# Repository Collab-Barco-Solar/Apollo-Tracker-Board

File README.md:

# Apollo-Tracker-Board
 
Projetos das PCB de transmissores e receptores, criadas no software KICAD 5.1.6.

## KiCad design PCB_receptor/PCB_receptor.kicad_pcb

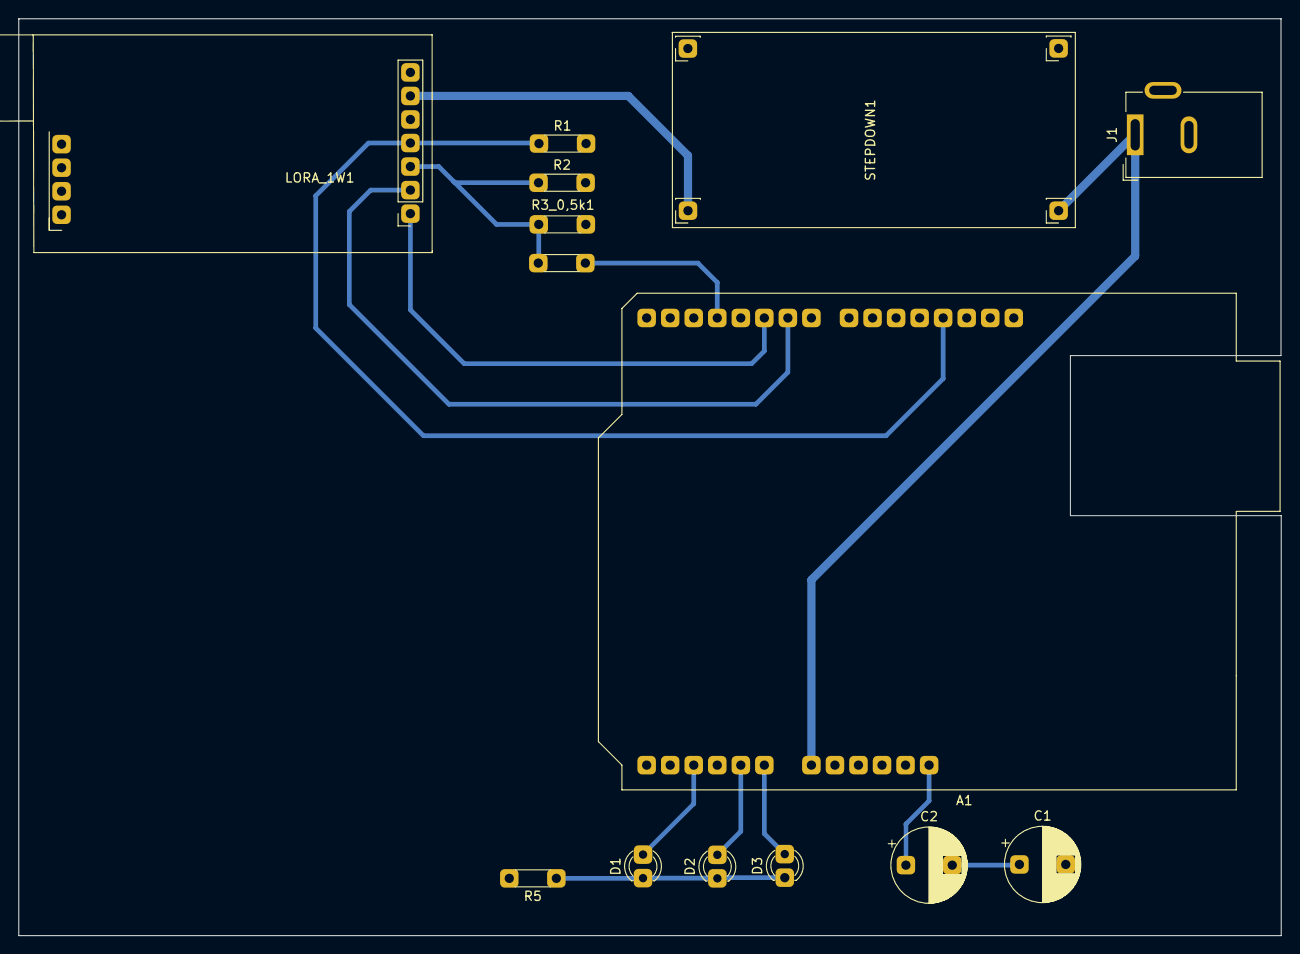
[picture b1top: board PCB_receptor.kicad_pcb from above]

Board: 2 copper layers, 136.2 x 98.9 mm, 14 parts (0 on the bottom side), 14 nets.

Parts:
1k1: R4_1k; R_Axial_DIN0204_L3.6mm_D1.6mm_P5.08mm_Horizontal
A1: Board_Ethernet_Shield_W5100-Arduino_Mega; Ethernet_Shield_W5100
C1, C2: 0,1uF; CP_Radial_D8.0mm_P5.00mm
D1, D2, D3: LED; LED_D3.0mm
J1: Barrel_Jack_MountingPin; BarrelJack_Wuerth_6941xx301002
LORA_1W1: LORA_433T30D; LORA_E32_433T30D
R1, R2: 4K7; R_Axial_DIN0204_L3.6mm_D1.6mm_P5.08mm_Horizontal
R3_0,5k1: R; R_Axial_DIN0204_L3.6mm_D1.6mm_P5.08mm_Horizontal
R5: 100; R_Axial_DIN0204_L3.6mm_D1.6mm_P5.08mm_Horizontal
STEPDOWN1: Converter_DCDC_STEPDOWN; STEPDOWN_XL4005

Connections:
3.3V_DCDC: LORA_1W1.6, STEPDOWN1.4
A0: A1.23, D3.2
A1: A1.24, D2.2
A3: A1.26, D1.2
GND: A1.2, A1.20, A1.21, C1.2, J1.2, LORA_1W1.7, R1.2, R2.2, R3_0,5k1.1, R5.2, STEPDOWN1.1, STEPDOWN1.3
GND_LED: D1.1, D2.1, D3.1, R5.1
M0: A1.11, LORA_1W1.1
M1: A1.10, LORA_1W1.2
unnamed: 1k1.2, A1.13
unnamed: C1.1, C2.2
RST: A1.17, C2.1
RX_LORA: 1k1.1, LORA_1W1.3, R2.1, R3_0,5k1.2
TX_LORA: A1.4, LORA_1W1.4, R1.1
VIN: A1.22, J1.1, STEPDOWN1.2

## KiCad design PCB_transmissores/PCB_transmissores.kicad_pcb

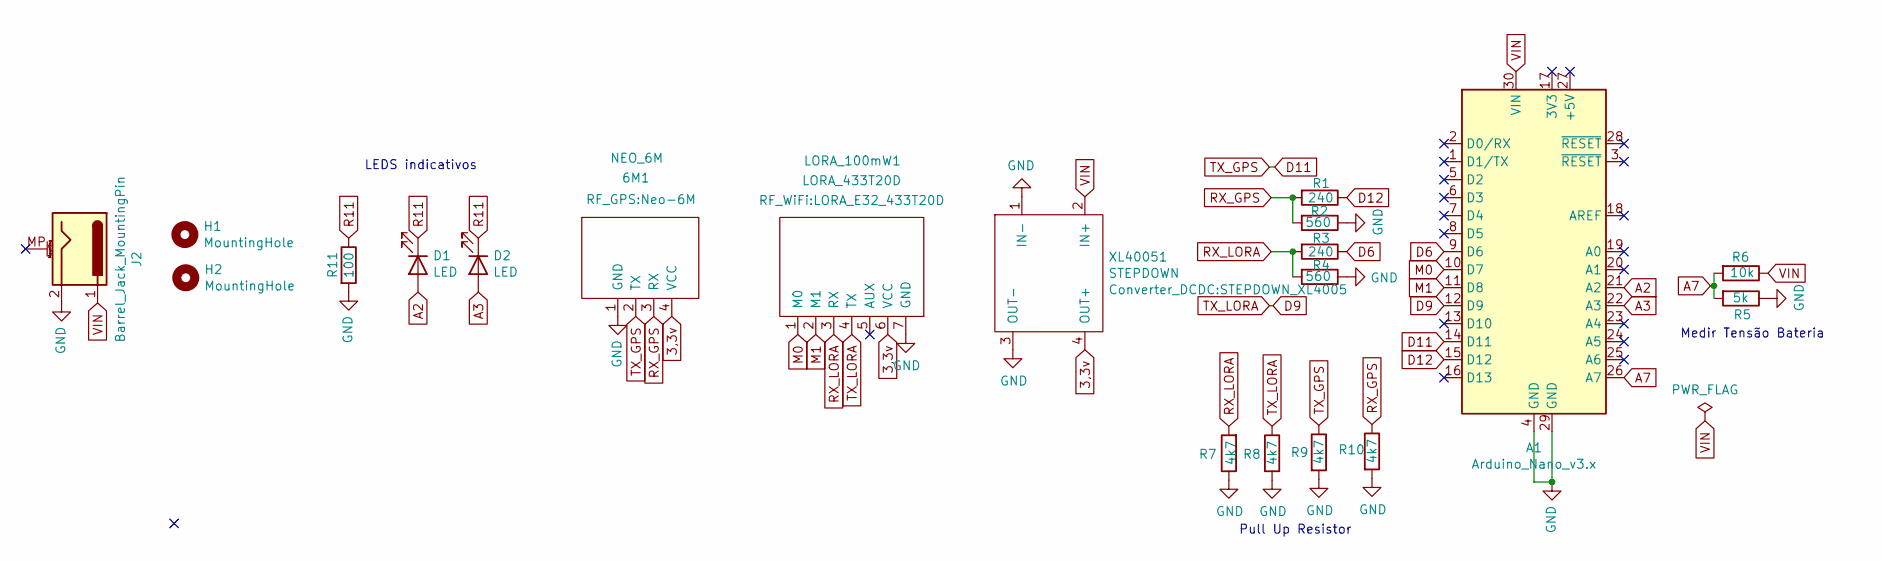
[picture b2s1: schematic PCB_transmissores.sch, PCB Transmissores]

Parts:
6M1: NEO_6M; Neo-6M
A1: Arduino_Nano_v3.x; Arduino_Nano
D1, D2: LED; LED_D5.0mm
H1, H2: MountingHole; MountingHole_5.5mm
J2: Barrel_Jack_MountingPin; BarrelJack_Wuerth_6941xx301002
LORA_100mW1: LORA_433T20D; LORA_E32_433T20D
R1, R3: 240; R_Axial_DIN0207_L6.3mm_D2.5mm_P7.62mm_Horizontal
R2, R4: 560; R_Axial_DIN0207_L6.3mm_D2.5mm_P7.62mm_Horizontal
R5: 5k; R_Axial_DIN0207_L6.3mm_D2.5mm_P7.62mm_Horizontal
R6: 10k; R_Axial_DIN0207_L6.3mm_D2.5mm_P7.62mm_Horizontal
R7, R8, R9, R10: 4k7; R_Axial_DIN0207_L6.3mm_D2.5mm_P7.62mm_Horizontal
R11: 100; R_Axial_DIN0207_L6.3mm_D2.5mm_P7.62mm_Horizontal
XL40051: STEPDOWN; STEPDOWN_XL4005

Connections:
3,3v: 6M1.4 (VCC), LORA_100mW1.6 (VCC), XL40051.4 (OUT+)
A2: A1.21 (A2), D1.2 (A)
A3: A1.22 (A3), D2.2 (A)
A7: A1.26 (A7), R5.2, R6.2
D6: A1.9 (D6), R3.1
D9: A1.12 (D9), LORA_100mW1.4 (TX), R8.1
D11: 6M1.2 (TX), A1.14 (D11), R9.1
D12: A1.15 (D12), R1.1
GND: 6M1.1 (GND), A1.4 (GND), A1.29 (GND), J2.2, LORA_100mW1.7 (GND), R2.1, R4.1, R5.1, R7.1, R8.2, R9.2, R10.2, R11.2, XL40051.1 (IN-), XL40051.3 (OUT-)
M0: A1.10 (D7), LORA_100mW1.1 (M0)
M1: A1.11 (D8), LORA_100mW1.2 (M1)
R11: D1.1 (K), D2.1 (K), R11.1
RX_GPS: 6M1.3 (RX), R1.2, R2.2, R10.1
RX_LORA: LORA_100mW1.3 (RX), R3.2, R4.2, R7.2
VIN: A1.30 (VIN), J2.1, R6.1, XL40051.2 (IN+)

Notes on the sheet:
Pull Up Resistor
Medir Tensão Bateria
LEDS indicativos

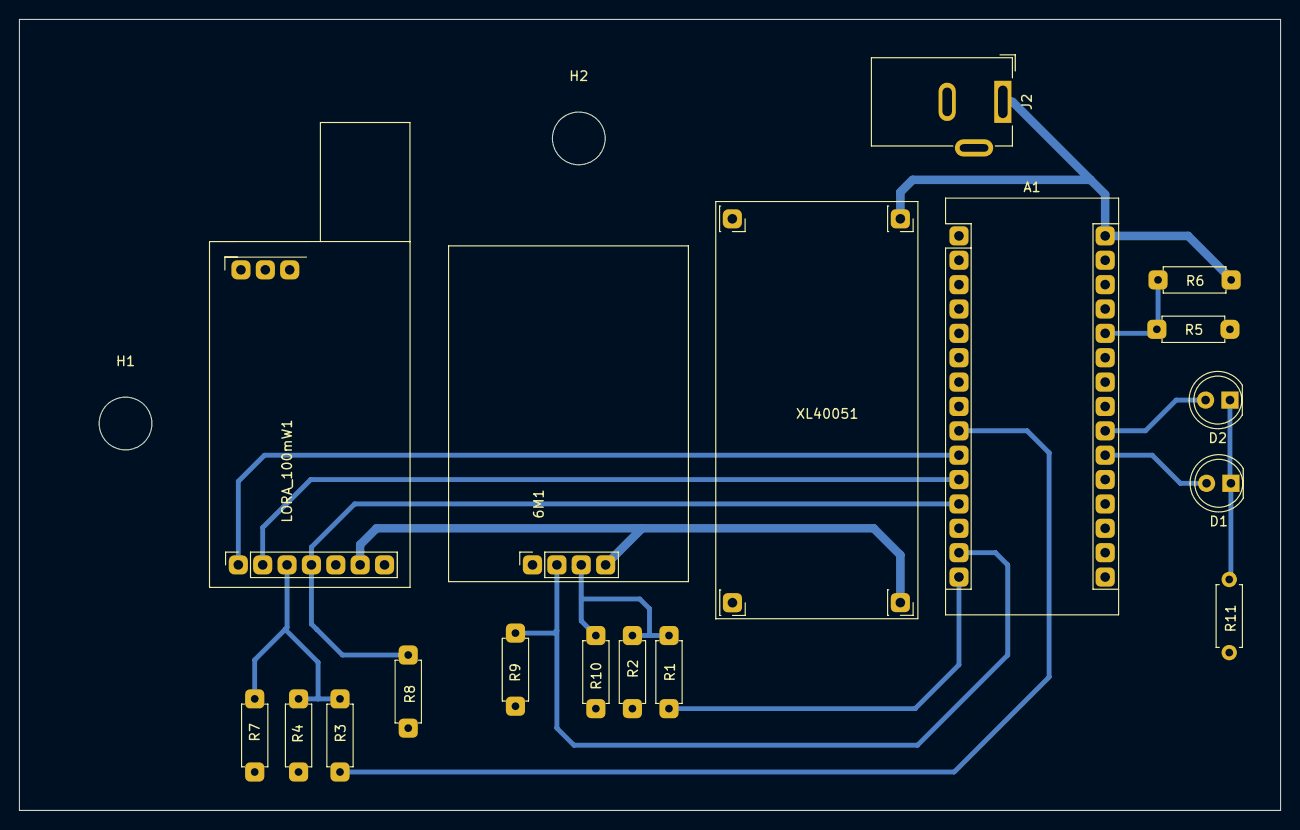
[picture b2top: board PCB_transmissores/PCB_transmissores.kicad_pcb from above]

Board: 2 copper layers, 131.4 x 82.4 mm, 20 parts (0 on the bottom side), 15 nets.

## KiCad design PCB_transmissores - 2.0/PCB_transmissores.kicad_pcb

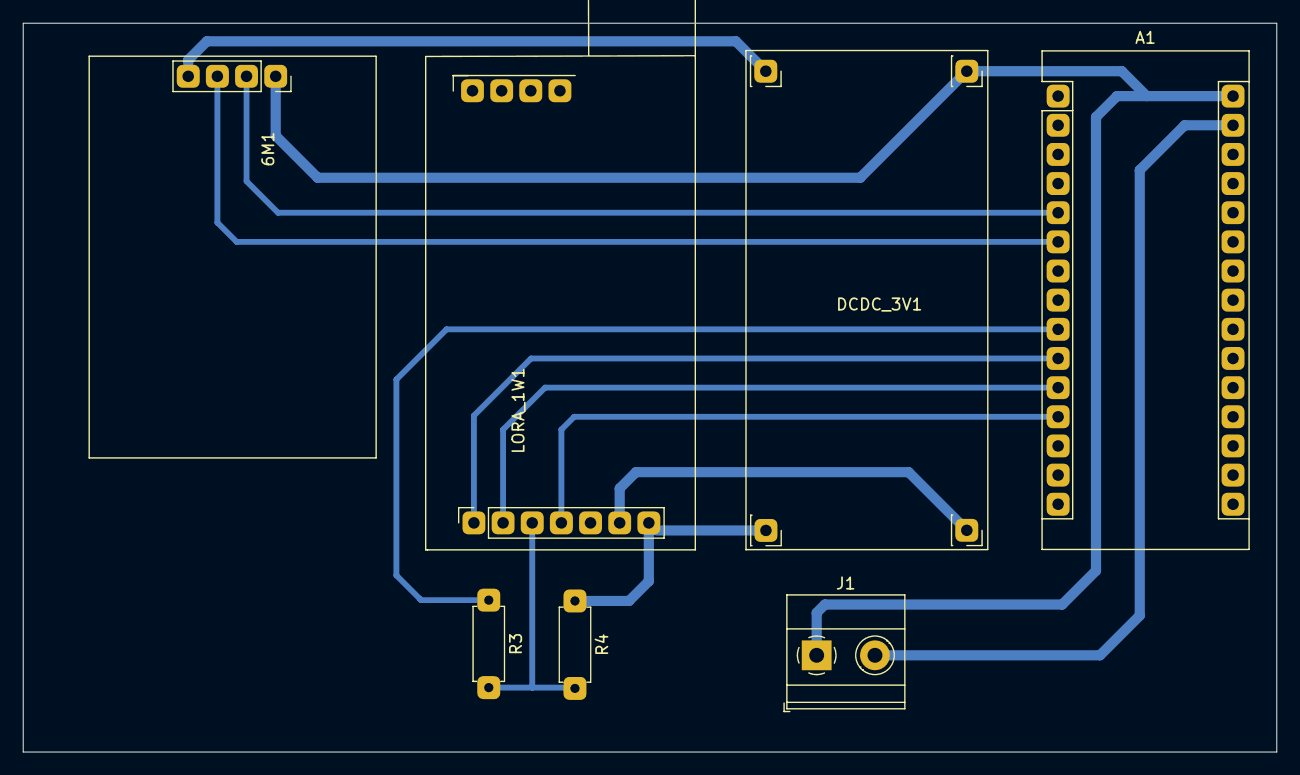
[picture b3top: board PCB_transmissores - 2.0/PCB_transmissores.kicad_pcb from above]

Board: 2 copper layers, 109.2 x 63.5 mm, 7 parts (0 on the bottom side), 10 nets.

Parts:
6M1: NEO_6M; Neo-6M
A1: Arduino_Nano_v3.x; Arduino_Nano
DCDC_3V1: DCDC_CHINA; STEPDOWN_CHINA
J1: Screw_Terminal_01x02; TerminalBlock_Phoenix_MKDS-1,5-2-5.08_1x02_P5.08mm_Horizont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
LORA_1W1: LORA_433T30D; LORA_E32_433T30D
R3: 1k; R_Axial_DIN0207_L6.3mm_D2.5mm_P7.62mm_Horizontal
R4: 0,5k; R_Axial_DIN0207_L6.3mm_D2.5mm_P7.62mm_Horizontal

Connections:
3.3V_DCDC: DCDC_3V1.4, LORA_1W1.6
GND: 6M1.1, A1.4, A1.29, DCDC_3V1.1, DCDC_3V1.3, J1.2, LORA_1W1.7, R4.1
M0: A1.10, LORA_1W1.1
M1: A1.11, LORA_1W1.2
unnamed: A1.9, R3.1
RX_GPS: 6M1.3, A1.5
RX_LORA: LORA_1W1.3, R3.2, R4.2
TX_GPS: 6M1.2, A1.6
TX_LORA: A1.12, LORA_1W1.4
VIN: 6M1.4, A1.30, DCDC_3V1.2, J1.1

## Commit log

2020-05-25 Subindo Primeiros Arquivos da Placa do Transmissor
    Primeiro upload dos arquivos da placa dos transmissores (KICAD)
2020-05-27 Pasta Renomeada
    Feita renomeação da pasta de "PCB_transmissores - 2.0" para "PCB_transmissores", apenas para fim de padronização.
2020-05-27 PCB do receptor
    Primeira versão da PCB do receptor
2020-05-27 Descrição
2020-06-21 Adicionado furos de fixação
    Adicionado furos de fixação
2020-06-21 Modificações placa transmissores
    Adicionado:
    Suporte de bateria
    Furos de fixação
    Resistores divisores de tensão
    Corrigida a posição dos pinos do módulo GPS
2020-07-26 Subtituito StepDown por StepUp
    Substituido o uso do StepDown DcDc por StepUp DcDc.
    Feitas modificações em trilhas e ligações para adaptar o circuito a mudança.
2020-11-16 atualização da placa dos transmissores
    Up
2020-12-02 Placa do Receptor atualizada
    Adicionados:
    LED's indicativos
    Capacitores para solucinonar defeito de fábrica da Shield Ethernet
    Resistores para divisor de tensão e Pull-Up
    Disposição dos componentes na placa refeito
2020-12-02 Placa dos transmissores atualizado
    Algumas trilhas refeitas
2020-12-24 Atualização placa do receptor
    Up
2020-12-24 Atualização placa dos transmissores
    Up
2020-12-24 Bibliotecas adicionais símbolos e footprints
    Bibliotecas com os simbolos e footprints adicionais necessários para o projeto.
    Passo a passo de como adicionar as bibliotecas ao kicad com imagens.
2020-12-31 PCB Receptores Atualização
    Up
